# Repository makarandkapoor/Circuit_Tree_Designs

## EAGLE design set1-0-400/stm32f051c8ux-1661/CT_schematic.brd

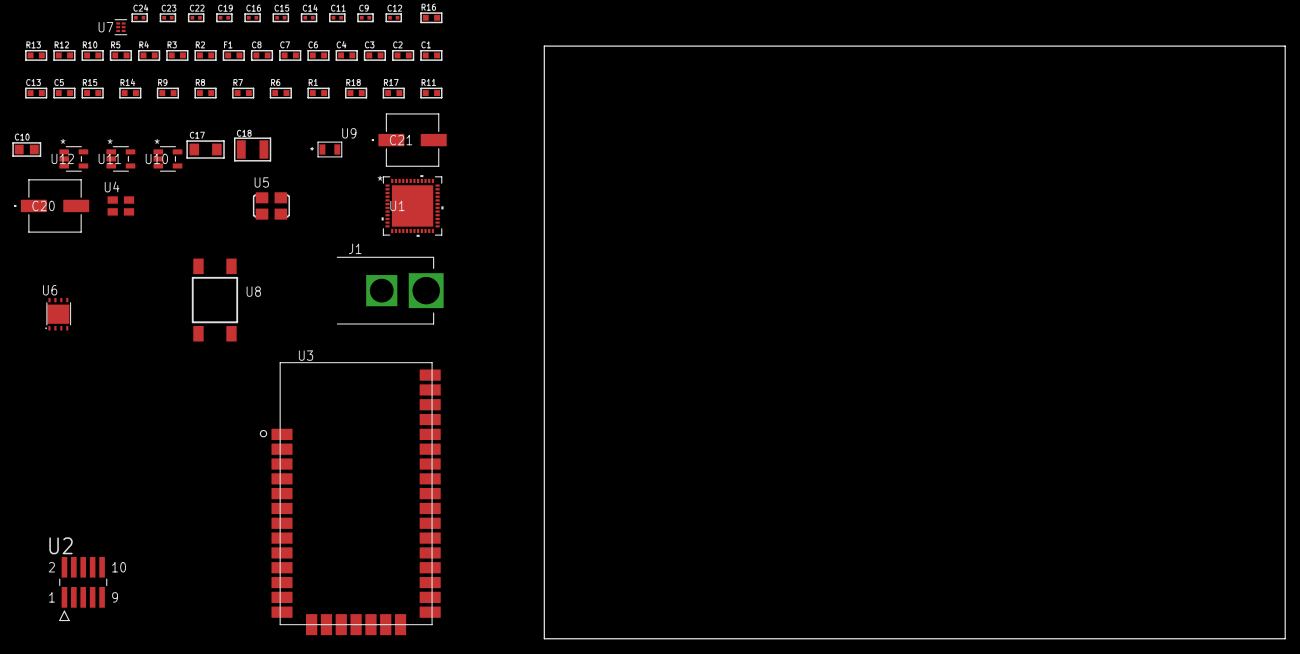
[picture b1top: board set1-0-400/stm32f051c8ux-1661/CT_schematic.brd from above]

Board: 2 copper layers, 100.0 x 80.0 mm, 56 parts (0 on the bottom side), 26 nets, no tracks yet.

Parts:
C1, C8: 1e-06; C0603
C2, C3, C4, C6: 1e-07; C0603
C5: 4.7e-06; C0603
C7: 1e-08; C0603
C9, C11, C19: 1e-07; C0402
C10: 1e-05; C0805
C12: 4.7e-11; C0402
C13: 8.2e-12; C0603
C14, C15, C16, C22, C23, C24: 1e-08; C0402
C17: 1e-05; C1206
C18: 1e-05; C1210
C20, C21: 0.0001; EXV-9H
F1: 240.0; L0603
J1: PJ-037B; PJ-037B_PACKAGE
R1, R6, R7, R8, R9, R14, R15: 10000.0; R0603
R2, R13: 1000.0; R0603
R3: 1600.5; R0603
R4, R5: 4700.0; R0603
R10: 5.0; R0603
R11: 100000.0; R0603
R12: 2231.0; R0603
R16: 9100.0; R0603
R17: 680000.0; R0603
R18: 120000.0; R0603
U1: stm32f051c8u7; UFQFPN48
U2: FTSH-105-01-L-DV-K; SAMTEC_FTSH-105-01-L-DV-K
U3: XB24CZ7UIS-004
U4: ASEK-32.768KHz-ECST; ASEK
U5: ASFL1-25MHZ-NCS; ASFL1
U6: LP3878SDX-ADJ/NOPB; WSON-8
U7: TPS3895ADRYR; SON-6
U8: 4-1437565-2; SW_4-1437565-2
U9: Q65110A2395; LGM67K-G1J2-24-Z
U10, U11, U12: nc7sz125m5x; NC7SZ125M5X

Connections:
CLK_U1_3: U1.3, U4.3
CLK_U1_5: U1.5, U5.3
GND: C1.2, C2.2, C3.2, C4.2, C5.2, C6.2, C7.2, C8.2, C9.2, C10.2, C11.2, C12.2, C13.2, C14.2, C15.2, C16.2, C17.2, C18.2, C19.2, C20.2, C21.2, C22.2, C23.2, C24.2, J1.2, R2.2, R6.2, R10.2, R13.2, R16.2, R18.2, U1.8, U1.23, U1.47, U1.49, U2.3, U2.5, U3.1, U3.11, U3.13, U3.22, U3.35, U4.2, U5.2, U6.3, U6.PAD, U7.2, U9.C, U10.2, U10.3, U11.1, U11.3, U12.1, U12.3
NET_U1_7: R5.1, U1.7, U12.4
NET_U1_9: C7.1, C8.1, F1.1, U1.9
NET_U1_44: R6.1, U1.44
NET_U1_45: R3.1, U1.45, U9.A
NET_U1_46: R1.1, U1.46, U8.3, U8.4
NET_U2_9: R10.1, U2.9
NET_U3_6: R4.1, U3.6, U11.4
NET_U6_1: C16.1, U6.1
NET_U6_6: R12.2, R13.1, U6.6
NET_U6_8: R11.1, U6.8
NET_U7_1: R15.1, R16.1, U7.1
NET_U7_3: R17.2, R18.1, U7.3
NET_U7_4: R14.1, U7.4, U10.4, U11.2, U12.2
NET_U8_1: R2.1, U8.1, U8.2
PROC_SPI1_MISO: U1.16, U3.17
PROC_SPI1_MOSI: U1.17, U3.16
PROC_SPI1_NSS: U1.14, U3.15
PROC_SPI1_SCK: U1.15, U3.14
PROC_SYS_SWCLK: R8.1, U1.37, U2.4
PROC_SYS_SWDIO: R9.1, U1.34, U2.2
RST_OUT_U2_JTAG_RST_B: R7.1, U2.10, U10.1
VCC_S1_10V0: C17.1, C20.1, C21.1, J1.1, R11.2, U6.4
VCC_TIER1_3V3: C1.1, C2.1, C3.1, C4.1, C5.1, C6.1, C9.1, C10.1, C11.1, C12.1, C13.1, C14.1, C15.1, C18.1, C19.1, C22.1, C23.1, C24.1, F1.2, R1.2, R3.2, R4.2, R5.2, R7.2, R8.2, R9.2, R12.1, R14.2, R15.2, R17.1, U1.1, U1.24, U1.48, U2.1, U3.2, U3.27, U4.4, U5.4, U6.5, U7.6, U10.5, U11.5, U12.5

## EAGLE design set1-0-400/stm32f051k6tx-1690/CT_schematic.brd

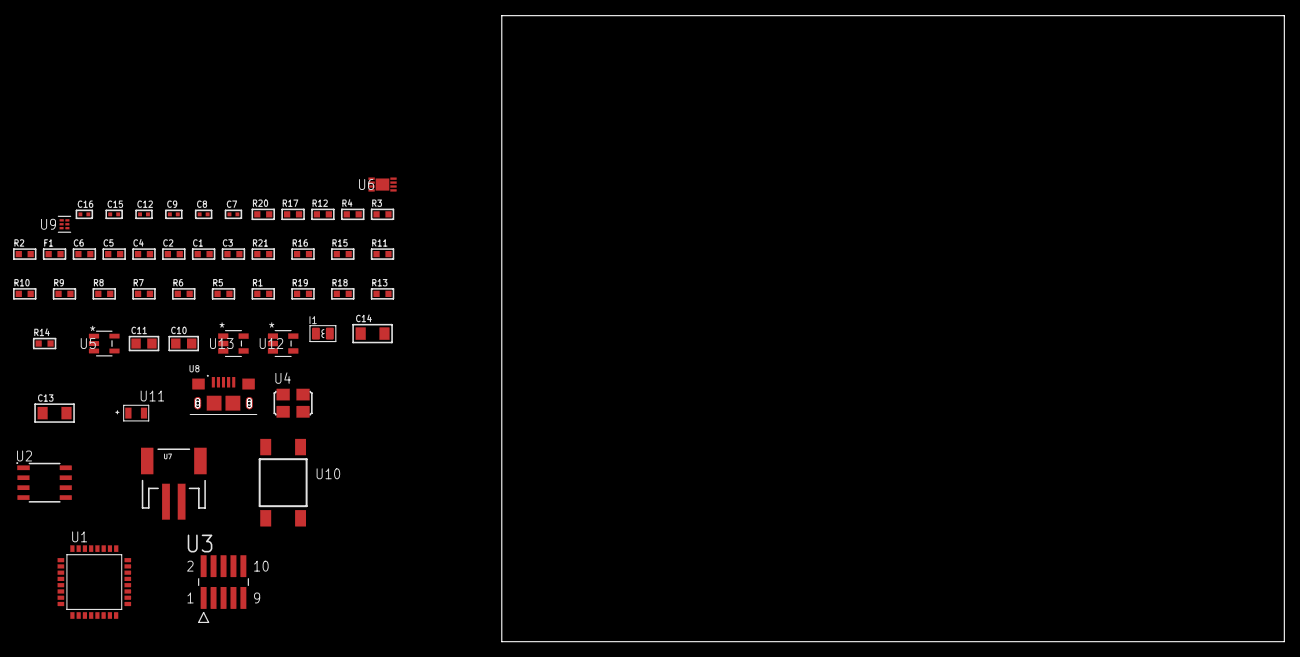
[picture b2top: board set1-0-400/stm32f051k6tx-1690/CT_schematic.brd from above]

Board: 2 copper layers, 52 parts (0 on the bottom side), 29 nets, no tracks yet.

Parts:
C1, C2: 1e-07; C0603
C3: 4.7e-06; C0603
C4, C5: 1e-08; C0603
C6: 1e-06; C0603
C7, C9, C15, C16: 1e-08; C0402
C8, C12: 1e-07; C0402
C10, C11: 1e-05; C0805
C13, C14: 1e-05; C1206
F1: 240.0; L0603
I1: 3.3e-06; L0806
R1, R5, R6, R7, R8, R9, R10, R11, R15, R16, R21: 10000.0; R0603
R2: 1000.0; R0603
R3: 1600.5; R0603
R4: 4700.0; R0603
R12: 5.0; R0603
R13: 220000.0; R0603
R14: 1000000.0; R0603
R17: 9100.0; R0603
R18: 680000.0; R0603
R19: 120000.0; R0603
R20: 2000.0; R0603
U1: stm32f051k6t6; LQFP32
U2: AT25M02-SSHD-T; SOIC-8
U3: FTSH-105-01-L-DV-K; SAMTEC_FTSH-105-01-L-DV-K
U4: ASFL1-25MHZ-NCS; ASFL1
U5: ltc3406es5; TSOT-23-5
U6: MCP73831T-2ACI/MC; DFN8_2X3MC
U7: S2B-PH-SM4-TB(LF)(SN); JST-2-SMD
U8: 10118193-0001LF; FCI_10118193-0001LF
U9: TPS3895ADRYR; SON-6
U10: 4-1437565-2; SW_4-1437565-2
U11: Q65110A2395; LGM67K-G1J2-24-Z
U12, U13: nc7sz125m5x; NC7SZ125M5X

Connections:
CLK_U1_2: U1.2, U4.3
GND: C1.2, C2.2, C3.2, C4.2, C5.2, C6.2, C7.2, C8.2, C9.2, C10.2, C11.1, C11.2, C12.2, C13.2, C14.2, C15.2, C16.2, R2.2, R5.2, R12.2, R13.2, R17.2, R19.2, R20.2, U1.16, U1.32, U2.4, U3.3, U3.5, U4.2, U5.2, U6.6, U6.9, U7.2, U8.5, U8.6, U8.7, U8.8, U8.9, U9.2, U11.C, U12.2, U12.3, U13.1, U13.3
INPUT_USBPOWER_5V: C13.1, R21.2, U6.1, U6.2, U8.1
NET_U1_4: R4.1, U1.4, U13.4
NET_U1_5: C4.1, C5.1, C6.1, F1.1, U1.5
NET_U1_29: R3.1, U1.29, U11.A
NET_U1_30: R1.1, U1.30, U10.3, U10.4
NET_U1_31: R5.1, U1.31
NET_U2_3: R6.1, U2.3
NET_U2_7: R8.1, U2.7
NET_U3_9: R12.1, U3.9
NET_U5_3: I1.1, U5.3
NET_U5_5: R13.1, R14.1, U5.5
NET_U5_ATNET_3: I1.2, R14.2
NET_U6_5: R21.1, U6.5
NET_U6_8: R20.1, U6.8
NET_U9_1: R16.1, R17.1, U9.1
NET_U9_3: R18.2, R19.1, U9.3
NET_U9_4: R15.1, U9.4, U12.4, U13.2
NET_U10_1: R2.1, U10.1, U10.2
PROC_SPI1_MISO: U1.12, U2.2
PROC_SPI1_MOSI: U1.13, U2.5
PROC_SPI1_NSS: R7.1, U1.10, U2.1
PROC_SPI1_SCK: U1.11, U2.6
PROC_SYS_SWCLK: R10.1, U1.24, U3.4
PROC_SYS_SWDIO: R11.1, U1.23, U3.2
RST_OUT_U3_JTAG_RST_B: R9.1, U3.10, U12.1
VCC_S1_3V7: C10.1, C14.1, U5.4, U6.3, U6.4, U7.1
VCC_TIER1_3V3: C1.1, C2.1, C3.1, C7.1, C8.1, C9.1, C11.2, C12.1, C15.1, C16.1, F1.2, I1.2, R1.2, R3.2, R4.2, R6.2, R7.2, R8.2, R9.2, R10.2, R11.2, R14.2, R15.2, R16.2, R18.1, U1.1, U1.17, U2.8, U3.1, U4.4, U9.6, U12.5, U13.5

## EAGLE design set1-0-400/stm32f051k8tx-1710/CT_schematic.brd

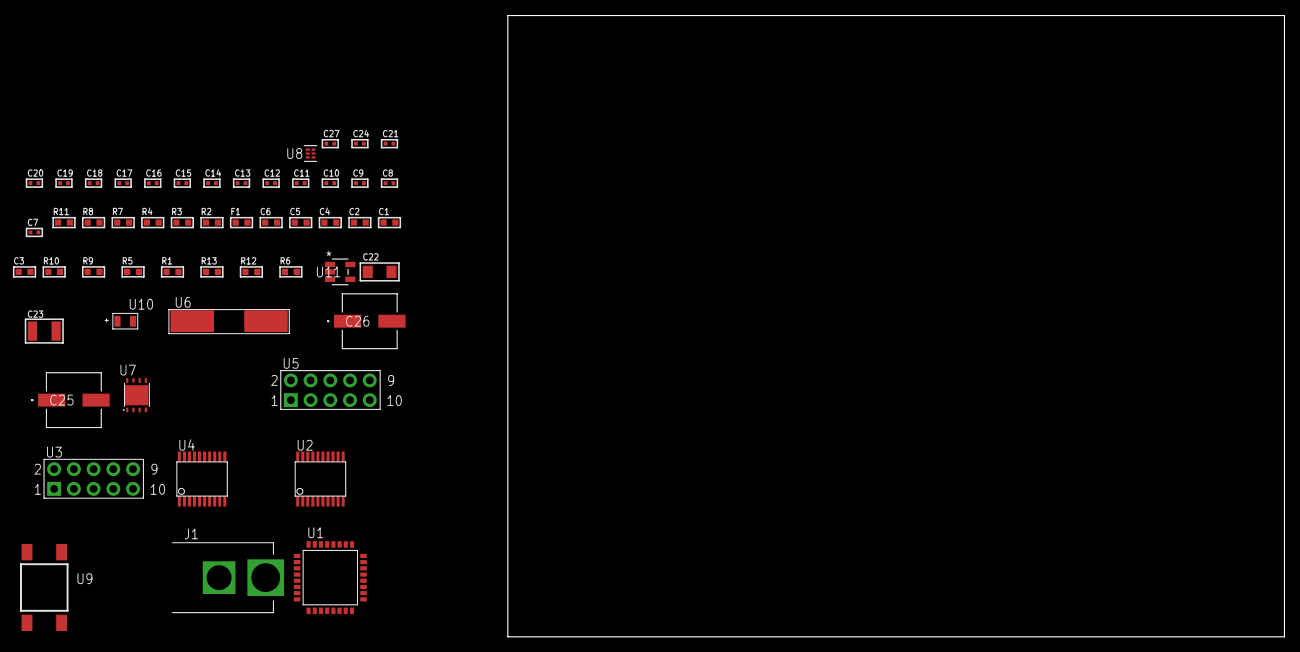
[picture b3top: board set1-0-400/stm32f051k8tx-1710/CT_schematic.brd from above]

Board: 2 copper layers, 100.0 x 80.0 mm, 53 parts (0 on the bottom side), 45 nets, no tracks yet.

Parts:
C1, C2: 1e-07; C0603
C3: 4.7e-06; C0603
C4, C5: 1e-08; C0603
C6: 1e-06; C0603
C7, C8: 1e-11; C0402
C9, C10, C11, C12, C13, C14, C15, C16, C17, C18, C19, C20, C24: 1e-07; C0402
C21, C27: 1e-08; C0402
C22: 1e-05; C1206
C23: 1e-05; C1210
C25, C26: 0.0001; EXV-9H
F1: 240.0; L0603
J1: PJ-037B; PJ-037B_PACKAGE
R1, R5, R9, R10: 10000.0; R0603
R2, R8: 1000.0; R0603
R3: 1600.5; R0603
R4: 4700.0; R0603
R6: 100000.0; R0603
R7: 2231.0; R0603
R11: 9100.0; R0603
R12: 680000.0; R0603
R13: 120000.0; R0603
U1: stm32f051k8t6; LQFP32
U2, U4: SP3203ECY-L/TR; TSSOP20-I
U3, U5: HTSS-105-01-G-D
U6: ABLS-25.000MHZ-B2F-T
U7: LP3878SDX-ADJ/NOPB; WSON-8
U8: TPS3895ADRYR; SON-6
U9: 4-1437565-2; SW_4-1437565-2
U10: Q65110A2395; LGM67K-G1J2-24-Z
U11: nc7sz125m5x; NC7SZ125M5X

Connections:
CLK_CRYSTAL_U1_2: C7.1, U1.2, U6.1
CLK_CRYSTAL_U1_3: C8.1, U1.3, U6.2
GND: C1.2, C2.2, C3.2, C4.2, C5.2, C6.2, C7.2, C8.2, C9.2, C10.2, C13.2, C14.2, C15.2, C16.2, C19.2, C20.2, C21.2, C22.2, C23.2, C24.2, C25.2, C26.2, C27.2, J1.2, R2.2, R5.2, R8.2, R11.2, R13.2, U1.16, U1.32, U2.18, U3.9, U4.18, U5.9, U7.3, U7.PAD, U8.2, U10.C, U11.1, U11.3
NET_U1_4: R4.1, U1.4, U11.4
NET_U1_5: C4.1, C5.1, C6.1, F1.1, U1.5
NET_U1_29: R3.1, U1.29, U10.A
NET_U1_30: R1.1, U1.30, U9.3, U9.4
NET_U1_31: R5.1, U1.31
NET_U2_1: C11.1, U2.1
NET_U2_2: C13.1, U2.2
NET_U2_3: C11.2, U2.3
NET_U2_4: C12.1, U2.4
NET_U2_5: C12.2, U2.5
NET_U2_6: C14.1, U2.6
NET_U3_3: U2.14, U3.3
NET_U3_4: U2.13, U3.4
NET_U3_5: U2.17, U3.5
NET_U3_6: U2.16, U3.6
NET_U4_1: C17.1, U4.1
NET_U4_2: C19.1, U4.2
NET_U4_3: C17.2, U4.3
NET_U4_4: C18.1, U4.4
NET_U4_5: C18.2, U4.5
NET_U4_6: C20.1, U4.6
NET_U5_3: U4.14, U5.3
NET_U5_4: U4.13, U5.4
NET_U5_5: U4.17, U5.5
NET_U5_6: U4.16, U5.6
NET_U7_1: C21.1, U7.1
NET_U7_6: R7.2, R8.1, U7.6
NET_U7_8: R6.1, U7.8
NET_U8_1: R10.1, R11.1, U8.1
NET_U8_3: R12.2, R13.1, U8.3
NET_U8_4: R9.1, U8.4, U11.2
NET_U9_1: R2.1, U9.1, U9.2
PROC_USART1_CTS: U1.21, U2.8
PROC_USART1_RTS: U1.22, U2.10
PROC_USART1_RX: U1.20, U2.11
PROC_USART1_TX: U1.19, U2.7
PROC_USART2_CTS: U1.6, U4.8
PROC_USART2_RTS: U1.7, U4.10
PROC_USART2_RX: U1.9, U4.11
PROC_USART2_TX: U1.8, U4.7
VCC_S1_7V8: C22.1, C25.1, C26.1, J1.1, R6.2, U7.4
VCC_TIER1_3V3: C1.1, C2.1, C3.1, C9.1, C10.1, C15.1, C16.1, C23.1, C24.1, C27.1, F1.2, R1.2, R3.2, R4.2, R7.1, R9.2, R10.2, R12.1, U1.1, U1.17, U2.12, U2.19, U4.12, U4.19, U7.5, U8.6, U11.5

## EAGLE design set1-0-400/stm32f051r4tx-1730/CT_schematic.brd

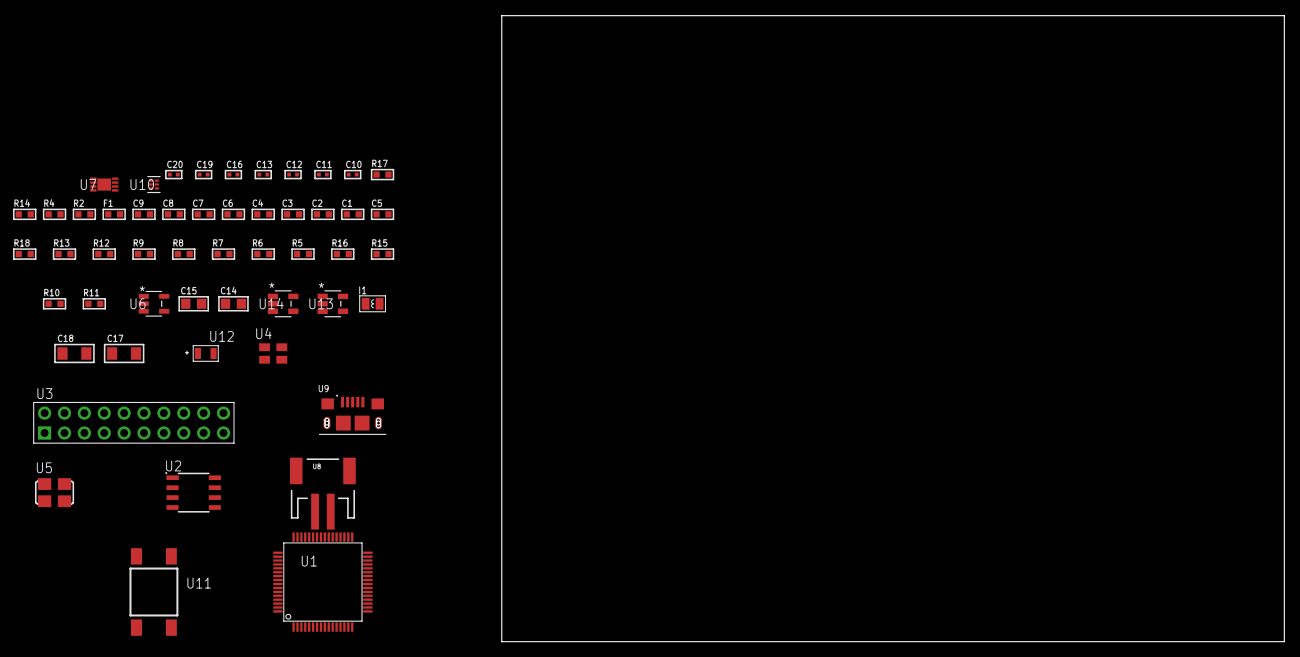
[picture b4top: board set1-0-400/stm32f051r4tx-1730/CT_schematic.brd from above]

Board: 2 copper layers, 122.6 x 80.0 mm, 52 parts (0 on the bottom side), 27 nets, no tracks yet.

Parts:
C1, C9: 1e-06; C0603
C2, C3, C4, C6, C7: 1e-07; C0603
C5: 4.7e-06; C0603
C8: 1e-08; C0603
C10, C12, C13, C19, C20: 1e-08; C0402
C11, C16: 1e-07; C0402
C14, C15: 1e-05; C0805
C17, C18: 1e-05; C1206
F1: 240.0; L0603
I1: 3.3e-06; L0806
R2: 1000.0; R0603
R4: 4700.0; R0603
R5, R6, R7, R8, R9, R12, R13, R18: 10000.0; R0603
R10: 220000.0; R0603
R11: 1000000.0; R0603
R14: 9100.0; R0603
R15: 680000.0; R0603
R16: 120000.0; R0603
R17: 2000.0; R0603
U1: stm32f051r4t6; LQFP64
U2: AT25040B-SSHL-T; SOIC-8
U3: TST-110-05-T-D-RA
U4: ASEK-32.768KHz-ECST; ASEK
U5: ASFL1-25MHZ-NCS; ASFL1
U6: ltc3406es5; TSOT-23-5
U7: MCP73831T-2ACI/MC; DFN8_2X3MC
U8: S2B-PH-SM4-TB(LF)(SN); JST-2-SMD
U9: 10118193-0001LF; FCI_10118193-0001LF
U10: TPS3895ADRYR; SON-6
U11: 4-1437565-2; SW_4-1437565-2
U12: Q65110A2395; LGM67K-G1J2-24-Z
U13, U14: nc7sz125m5x; NC7SZ125M5X

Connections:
CLK_U1_3: U1.3, U4.3
CLK_U1_5: U1.5, U5.3
GND: C1.2, C2.2, C3.2, C4.2, C5.2, C6.2, C7.2, C8.2, C9.2, C10.2, C11.2, C12.2, C13.2, C14.2, C15.1, C15.2, C16.2, C17.2, C18.2, C19.2, C20.2, R2.2, R5.2, R10.2, R14.2, R16.2, R17.2, U1.12, U1.31, U1.63, U2.4, U3.4, U3.6, U3.8, U3.10, U3.12, U3.14, U3.16, U3.18, U3.20, U4.2, U5.2, U6.2, U7.6, U7.9, U8.2, U9.5, U9.6, U9.7, U9.8, U9.9, U10.2, U12.C, U13.2, U13.3, U14.1, U14.3
INPUT_USBPOWER_5V: C17.1, R18.2, U7.1, U7.2, U9.1
NET_U1_7: R4.1, U1.7, U14.4
NET_U1_13: C8.1, C9.1, F1.1, U1.13
NET_U1_60: R5.1, U1.60
NET_U1_62: U11.3, U11.4
NET_U2_3: R6.1, U2.3
NET_U2_7: R8.1, U2.7
NET_U6_3: I1.1, U6.3
NET_U6_5: R10.1, R11.1, U6.5
NET_U6_ATNET_3: I1.2, R11.2
NET_U7_5: R18.1, U7.5
NET_U7_8: R17.1, U7.8
NET_U10_1: R13.1, R14.1, U10.1
NET_U10_3: R15.2, R16.1, U10.3
NET_U10_4: R12.1, U10.4, U13.4, U14.2
NET_U11_1: R2.1, U11.1, U11.2
PROC_SPI1_MISO: U1.22, U2.2
PROC_SPI1_MOSI: U1.23, U2.5
PROC_SPI1_NSS: R7.1, U1.20, U2.1
PROC_SPI1_SCK: U1.21, U2.6
PROC_SYS_SWDIO: U1.46, U3.7
RST_OUT_U3_SRESET_B: R9.1, U3.15, U13.1
VCC_S1_3V7: C14.1, C18.1, U6.4, U7.3, U7.4, U8.1
VCC_TIER1_3V3: C1.1, C2.1, C3.1, C4.1, C5.1, C6.1, C7.1, C10.1, C11.1, C12.1, C13.1, C15.2, C16.1, C19.1, C20.1, F1.2, I1.2, R4.2, R6.2, R7.2, R8.2, R9.2, R11.2, R12.2, R13.2, R15.1, U1.1, U1.32, U1.64, U2.8, U3.1, U4.4, U5.4, U10.6, U13.5, U14.5

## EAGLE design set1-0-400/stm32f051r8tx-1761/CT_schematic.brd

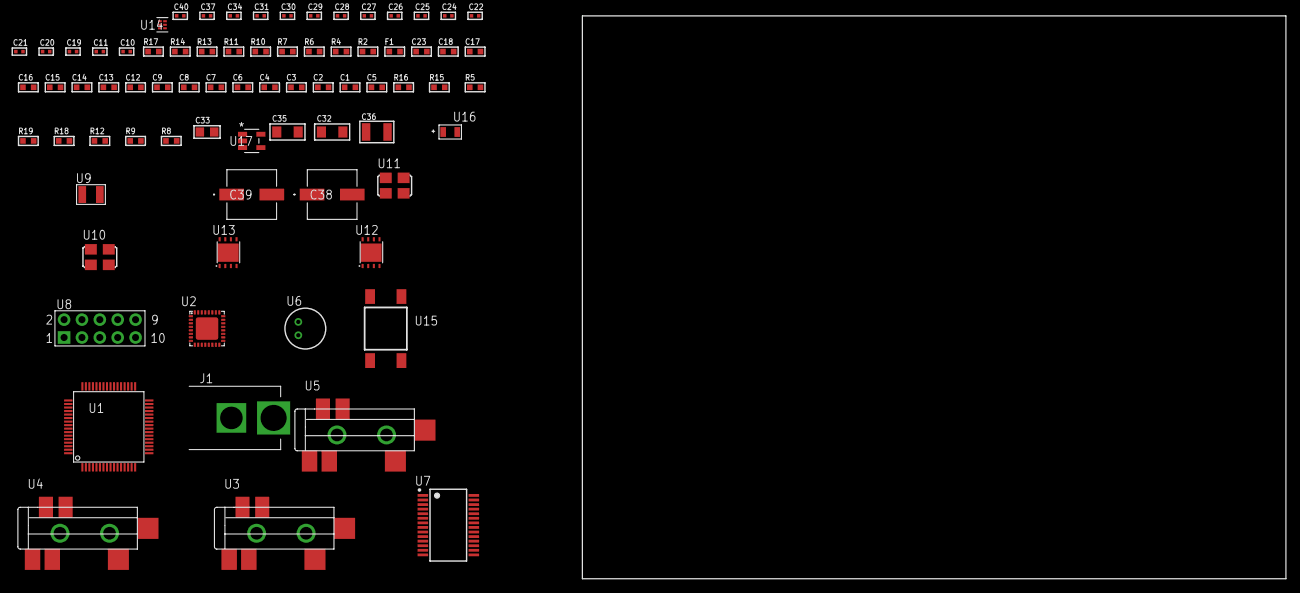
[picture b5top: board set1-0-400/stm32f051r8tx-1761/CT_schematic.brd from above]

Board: 2 copper layers, 100.0 x 80.0 mm, 76 parts (0 on the bottom side), 53 nets, no tracks yet.

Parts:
C1, C9, C12, C13, C14, C15, C16, C17, C18, C23: 1e-06; C0603
C2, C3, C4, C6, C7: 1e-07; C0603
C5: 4.7e-06; C0603
C8: 1e-08; C0603
C10, C11: 1e-11; C0402
C19, C20, C21, C22, C24, C25, C26, C27, C28, C37: 1e-07; C0402
C29, C30, C31, C34, C40: 1e-08; C0402
C32, C35: 1e-05; C1206
C33: 1e-05; C0805
C36: 1e-05; C1210
C38, C39: 0.0001; EXV-9H
F1: 240.0; L0603
J1: PJ-037B; PJ-037B_PACKAGE
R2, R11, R14: 1000.0; R0603
R4: 4700.0; R0603
R5, R15, R16: 10000.0; R0603
R6, R7: 1270.0; R0603
R8, R9, R12: 100000.0; R0603
R10: 200.0; R0603
R13: 2231.0; R0603
R17: 9100.0; R0603
R18: 680000.0; R0603
R19: 120000.0; R0603
U1: stm32f051r8t7; LQFP64
U2: SGTL5000XNAA3; QFN-32
U3, U4, U5: SJ-43515TS-SMT-TR
U6: WM-64PCT; WM-64PC
U7: ST3241EBPR; SSOP-28
U8: HTSS-105-01-G-D
U9: ABS07-32.768KHZ-7-T
U10: ASFL-24.57MHZ-NCS; ASFL1
U11: ASFL1-25MHZ-NCS; ASFL1
U12, U13: LP3878SDX-ADJ/NOPB; WSON-8
U14: TPS3895ADRYR; SON-6
U15: 4-1437565-2; SW_4-1437565-2
U16: Q65110A2395; LGM67K-G1J2-24-Z
U17: nc7sz125m5x; NC7SZ125M5X

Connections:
CLK_CRYSTAL_U1_3: C10.1, U1.3, U9.1
CLK_CRYSTAL_U1_4: C11.1, U1.4, U9.2
CLK_U1_5: U1.5, U11.3
CLK_U2_21: U2.21, U10.3
GND: C1.2, C2.2, C3.2, C4.2, C5.2, C6.2, C7.2, C8.2, C9.2, C10.2, C11.2, C19.2, C20.2, C21.2, C22.2, C23.2, C24.2, C27.2, C28.2, C29.2, C30.2, C31.2, C32.2, C33.2, C34.2, C35.2, C36.2, C37.2, C38.2, C39.2, C40.2, J1.2, R2.2, R5.2, R7.2, R11.2, R14.2, R17.2, R19.2, U1.12, U1.31, U1.63, U2.1, U2.3, U2.7, U2.EXP, U4.1, U5.1, U6.2, U7.23, U7.25, U8.9, U10.2, U11.2, U12.3, U12.PAD, U13.3, U13.PAD, U14.2, U16.C, U17.1, U17.3
NET_U1_7: R4.1, U1.7, U17.4
NET_U1_13: C8.1, C9.1, F1.1, U1.13
NET_U1_60: R5.1, U1.60
NET_U1_62: U15.3, U15.4
NET_U2_10: C22.1, U2.10
NET_U2_29: R6.1, U2.29
NET_U2_31: R7.1, U2.31
NET_U3_1: U2.4, U3.1
NET_U3_2: U2.2, U3.2
NET_U3_5: U2.6, U3.5
NET_U4_2: C13.1, U4.2
NET_U4_5: C12.1, U4.5
NET_U5_2: C15.1, C16.1, U5.2
NET_U5_5: C14.1, U5.5
NET_U5_13: C15.2, C16.2
NET_U6_1: C17.1, C18.1, C23.1, U2.16, U6.1
NET_U6_15: C17.2, C18.2
NET_U7_1: C26.1, U7.1
NET_U7_2: C26.2, U7.2
NET_U7_3: C28.1, U7.3
NET_U7_22: R8.1, U7.22
NET_U7_24: C25.2, U7.24
NET_U7_27: C27.1, U7.27
NET_U7_28: C25.1, U7.28
NET_U8_3: U7.4, U8.3
NET_U8_4: U7.5, U8.4
NET_U8_5: U7.9, U8.5
NET_U8_6: U7.10, U8.6
NET_U12_1: C31.1, U12.1
NET_U12_6: R10.2, R11.1, U12.6
NET_U12_8: R9.1, U12.8
NET_U13_1: C34.1, U13.1
NET_U13_6: R13.2, R14.1, U13.6
NET_U13_8: R12.1, U13.8
NET_U14_1: R16.1, R17.1, U14.1
NET_U14_3: R18.2, R19.1, U14.3
NET_U14_4: R15.1, U14.4, U17.2
NET_U15_1: R2.1, U15.1, U15.2
PROC_I2S1_CK: U1.21, U2.24
PROC_I2S1_SD: U1.23, U2.26
PROC_I2S1_WS: U1.20, U2.23
PROC_USART1_CTS: U1.44, U7.13
PROC_USART1_RTS: U1.45, U7.18
PROC_USART1_RX: U1.43, U7.19
PROC_USART1_TX: U1.42, U7.14
VCC_S1_8V6: C32.1, C35.1, C38.1, C39.1, J1.1, R9.2, R12.2, U12.4, U13.4
VCC_TIER1_1V2: C19.1, C33.1, R10.1, U2.30, U12.5
VCC_TIER1_3V3: C1.1, C2.1, C3.1, C4.1, C5.1, C6.1, C7.1, C20.1, C21.1, C24.1, C29.1, C30.1, C36.1, C37.1, C40.1, F1.2, R4.2, R6.2, R8.2, R13.1, R15.2, R16.2, R18.1, U1.1, U1.32, U1.64, U2.5, U2.20, U7.26, U10.4, U11.4, U13.5, U14.6, U17.5

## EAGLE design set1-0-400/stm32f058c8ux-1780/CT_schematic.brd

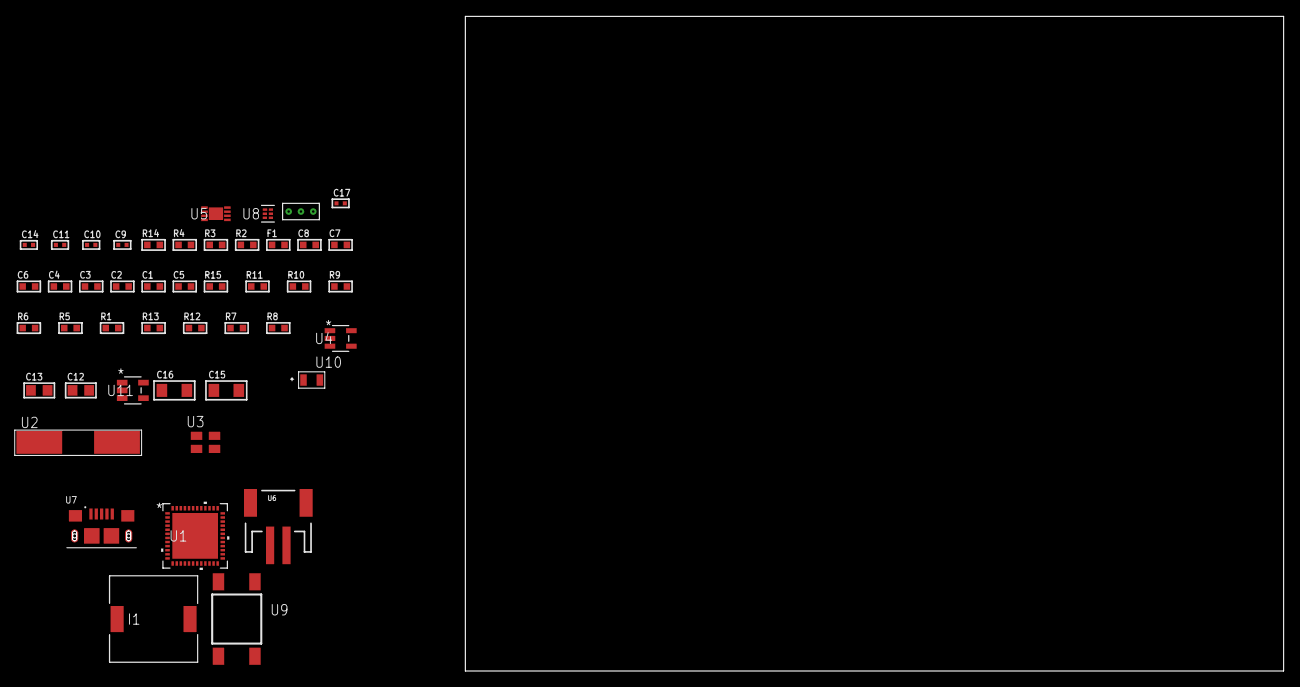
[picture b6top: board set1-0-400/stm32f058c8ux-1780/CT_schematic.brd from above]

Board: 2 copper layers, 148.0 x 80.0 mm, 46 parts (0 on the bottom side), 24 nets, no tracks yet.

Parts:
C1, C8: 1e-06; C0603
C2, C3, C4, C6: 1e-07; C0603
C5: 4.7e-06; C0603
C7: 1e-08; C0603
C9, C10: 1e-11; C0402
C11, C17: 1e-08; C0402
C12, C13: 1e-05; C0805
C14: 1e-07; C0402
C15, C16: 1e-05; C1206
F1: 240.0; L0603
I1: 7e-06; DR1040
R1, R5, R6, R9, R10, R15: 10000.0; R0603
R2: 1000.0; R0603
R3: 910.0; R0603
R4: 4700.0; R0603
R7: 490000.0; R0603
R8: 1000000.0; R0603
R11: 82000.0; R0603
R12: 300000.0; R0603
R13: 120000.0; R0603
R14: 2000.0; R0603
U1: stm32f058c8u7; UFQFPN48
U2: ABLS-25.000MHZ-B2F-T
U3: ASEK-2-32.768KHz-ECST; ASEK
U4: ltc3406es5; TSOT-23-5
U5: MCP73831T-2ACI/MC; DFN8_2X3MC
U6: S2B-PH-SM4-TB(LF)(SN); JST-2-SMD
U7: 10118193-0001LF; FCI_10118193-0001LF
U8: TPS3895ADRYR; SON-6
U9: 4-1437565-2; SW_4-1437565-2
U10: Q65110A2395; LGM67K-G1J2-24-Z
U11: nc7sz125m5x; NC7SZ125M5X
U12: Dummy; DUMMY_PACKAGE_93

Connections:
CLK_CRYSTAL_U1_5: C9.1, U1.5, U2.1
CLK_CRYSTAL_U1_6: C10.1, U1.6, U2.2
CLK_U1_3: U1.3, U3.3
GND: C1.2, C2.2, C3.2, C4.2, C5.2, C6.2, C7.2, C8.2, C9.2, C10.2, C11.2, C12.2, C13.1, C13.2, C14.2, C15.2, C16.2, C17.2, R2.2, R5.2, R6.2, R7.2, R11.2, R13.2, R14.2, U1.8, U1.23, U1.47, U1.49, U3.2, U4.2, U5.6, U5.9, U6.2, U7.5, U7.6, U7.7, U7.8, U7.9, U8.2, U10.C, U11.1, U11.3, U12.1
INPUT_USBPOWER_5V: C15.1, R15.2, U5.1, U5.2, U7.1
NET_U1_7: R4.1, U1.7, U11.4
NET_U1_9: C7.1, C8.1, F1.1, U1.9
NET_U1_20: R6.1, U1.20
NET_U1_44: R5.1, U1.44
NET_U1_45: R3.1, U1.45, U10.A
NET_U1_46: R1.1, U1.46, U9.3, U9.4
NET_U4_3: I1.1, U4.3
NET_U4_5: R7.1, R8.1, U4.5
NET_U4_ATNET_3: I1.2, R8.2
NET_U5_5: R15.1, U5.5
NET_U5_8: R14.1, U5.8
NET_U8_1: R10.1, R11.1, U8.1
NET_U8_3: R12.2, R13.1, U8.3
NET_U8_4: R9.1, U8.4, U11.2
NET_U9_1: R2.1, U9.1, U9.2
PROC_ADC_IN3: U1.13, U12.2
PROC_ADC_IN4: U1.14, U12.3
VCC_S1_3V7: C12.1, C16.1, U4.4, U5.3, U5.4, U6.1
VCC_TIER1_1V8: C1.1, C2.1, C3.1, C4.1, C5.1, C6.1, C11.1, C13.2, C14.1, C17.1, F1.2, I1.2, R1.2, R3.2, R4.2, R8.2, R9.2, R10.2, R12.1, U1.1, U1.24, U1.48, U3.4, U8.6, U11.5

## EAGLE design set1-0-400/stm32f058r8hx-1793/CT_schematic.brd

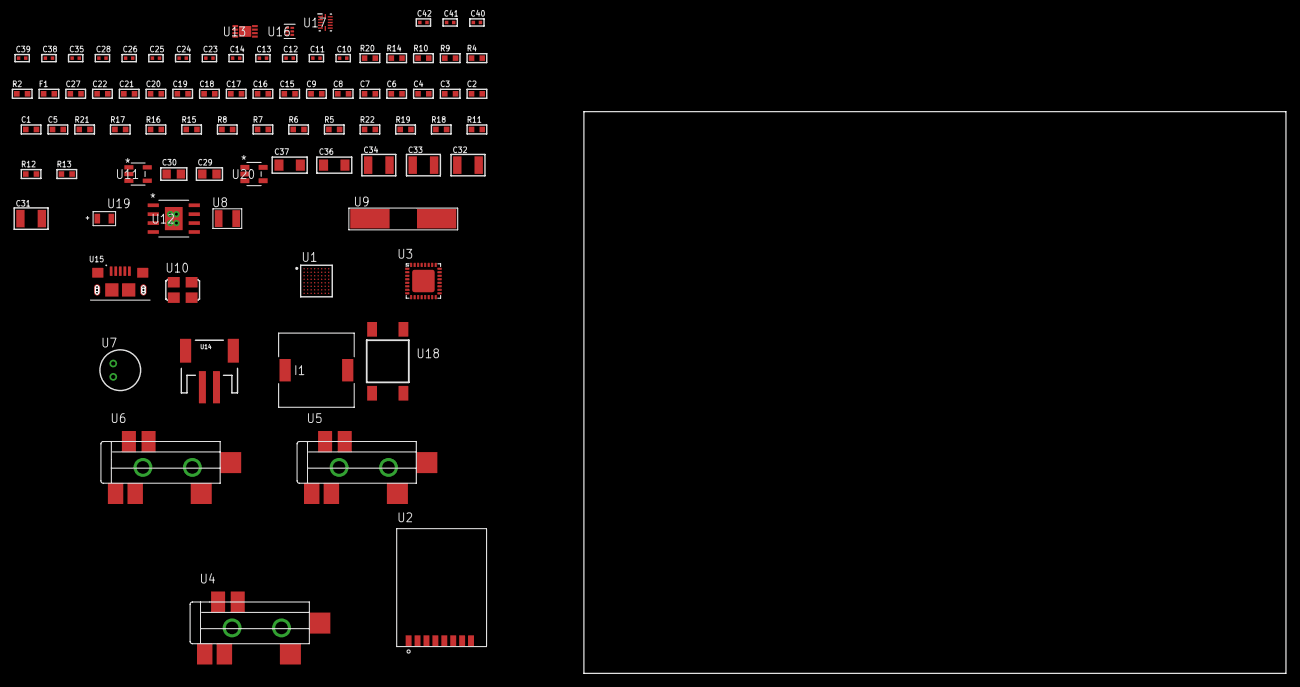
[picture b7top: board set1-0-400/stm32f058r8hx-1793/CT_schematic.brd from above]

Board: 2 copper layers, 84 parts (0 on the bottom side), 47 nets, no tracks yet.

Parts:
C1, C9, C15, C16, C17, C18, C19, C20, C21, C22, C27: 1e-06; C0603
C2, C3, C4, C6, C7: 1e-07; C0603
C5: 4.7e-06; C0603
C8: 1e-08; C0603
C10, C11, C12, C13: 1e-11; C0402
C14, C23, C24, C25, C26, C35, C39, C41: 1e-07; C0402
C28, C38, C40, C42: 1e-08; C0402
C29, C30: 1e-05; C0805
C31, C32, C33, C34: 1e-05; C1210
C36, C37: 1e-05; C1206
F1: 240.0; L0603
I1: 3.8e-06; DR1040
R2: 1000.0; R0603
R4: 4700.0; R0603
R5, R6, R7, R8, R15, R16, R21: 10000.0; R0603
R9, R10: 1270.0; R0603
R11: 490000.0; R0603
R12: 1000000.0; R0603
R13: 4031.5447154472; R0603
R14: 2200.0; R0603
R17: 82000.0; R0603
R18: 300000.0; R0603
R19: 120000.0; R0603
R20: 2000.0; R0603
R22: 200000.0; R0603
U1: stm32f058r8h7; UFBGA64
U2: RFM75-S
U3: SGTL5000XNAA3; QFN-32
U4, U5, U6: SJ-43515TS-SMT-TR
U7: WM-64PCT; WM-64PC
U8: ABS07-32.768KHZ-7-T
U9: ABLS-25.000MHZ-B2F-T
U10: ASFL-24.57MHZ-NCS; ASFL1
U11: ltc3406es5; TSOT-23-5
U12: MIC5234YME; SOIC-8_EP
U13: MCP73831T-2ACI/MC; DFN8_2X3MC
U14: S2B-PH-SM4-TB(LF)(SN); JST-2-SMD
U15: 10118193-0001LF; FCI_10118193-0001LF
U16: TPS3895ADRYR; SON-6
U17: LSF0204DRUTR; RUT0012A
U18: 4-1437565-2; SW_4-1437565-2
U19: Q65110A2395; LGM67K-G1J2-24-Z
U20: nc7sz125m5x; NC7SZ125M5X

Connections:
CLK_CRYSTAL_U1_A1: C10.1, U1.A1, U8.1
CLK_CRYSTAL_U1_B1: C11.1, U1.B1, U8.2
CLK_CRYSTAL_U1_C1: C12.1, U1.C1, U9.1
CLK_CRYSTAL_U1_D1: C13.1, U1.D1, U9.2
CLK_U3_21: U3.21, U10.3
GND: C1.2, C2.2, C3.2, C4.2, C5.2, C6.2, C7.2, C8.2, C9.2, C10.2, C11.2, C12.2, C13.2, C14.2, C15.2, C23.2, C24.2, C25.2, C26.2, C27.2, C28.2, C29.2, C30.1, C30.2, C31.2, C32.2, C33.2, C34.2, C35.2, C36.2, C37.2, C38.2, C39.2, C40.2, C41.2, C42.2, R2.2, R5.2, R6.2, R10.2, R11.2, R14.2, R17.2, R19.2, R20.2, U1.D4, U1.D5, U1.F1, U2.1, U3.1, U3.3, U3.7, U3.EXP, U5.1, U6.1, U7.2, U10.2, U11.2, U12.7, U12.EPAD, U13.6, U13.9, U14.2, U15.5, U15.6, U15.7, U15.8, U15.9, U16.2, U17.6, U19.C, U20.1, U20.3
INPUT_USBPOWER_5V: C36.1, R21.2, U13.1, U13.2, U15.1
NET_U1_B4: R5.1, U1.B4
NET_U1_E1: R4.1, U1.E1, U20.4
NET_U1_G6: R6.1, U1.G6
NET_U1_H1: C8.1, C9.1, F1.1, U1.H1
NET_U1_H8: U18.3, U18.4
NET_U2_3: R7.1, U2.3
NET_U3_10: C26.1, U3.10
NET_U3_29: R9.1, U3.29
NET_U3_31: R10.1, U3.31
NET_U4_1: U3.4, U4.1
NET_U4_2: U3.2, U4.2
NET_U4_5: U3.6, U4.5
NET_U5_2: C17.1, U5.2
NET_U5_5: C16.1, U5.5
NET_U6_2: C19.1, C20.1, U6.2
NET_U6_5: C18.1, U6.5
NET_U6_13: C19.2, C20.2
NET_U7_1: C21.1, C22.1, C27.1, U3.16, U7.1
NET_U7_15: C21.2, C22.2
NET_U11_3: I1.1, U11.3
NET_U11_5: R11.1, R12.1, U11.5
NET_U11_ATNET_3: I1.2, R12.2
NET_U12_4: R13.2, R14.1, U12.4
NET_U13_5: R21.1, U13.5
NET_U13_8: R20.1, U13.8
NET_U16_1: R16.1, R17.1, U16.1
NET_U16_3: R18.2, R19.1, U16.3
NET_U16_4: R15.1, U16.4, U20.2
NET_U17_12: R22.1, U17.12
NET_U18_1: R2.1, U18.1, U18.2
PROC_I2S1_CK: U1.A5, U3.24
PROC_I2S1_SD: U1.C4, U3.26
PROC_I2S1_WS: U1.A6, U3.23
PROC_SPI1_MISO_TOXCVR: U2.7, U17.9
PROC_SPI1_MOSI_TOXCVR: U2.6, U17.10
PROC_SPI1_NSS_TOXCVR: R8.1, U2.4, U17.7
PROC_SPI1_SCK_TOXCVR: U2.5, U17.8
VCC_S1_3V7: C29.1, C31.1, C32.1, C37.1, U11.4, U12.5, U12.8, U13.3, U13.4, U14.1
VCC_TIER1_1V8: C1.1, C2.1, C3.1, C4.1, C5.1, C6.1, C7.1, C23.1, C24.1, C25.1, C30.2, C35.1, C40.1, C41.1, C42.1, F1.2, I1.2, R4.2, R9.2, R12.2, R15.2, R16.2, R18.1, R22.2, U1.B2, U1.E4, U1.E5, U3.5, U3.20, U3.30, U16.6, U17.1, U20.5
VCC_TIER1_3V3: C14.1, C15.1, C28.1, C33.1, C34.1, C38.1, C39.1, R7.2, R8.2, R13.1, U2.2, U10.4, U12.1, U17.11
